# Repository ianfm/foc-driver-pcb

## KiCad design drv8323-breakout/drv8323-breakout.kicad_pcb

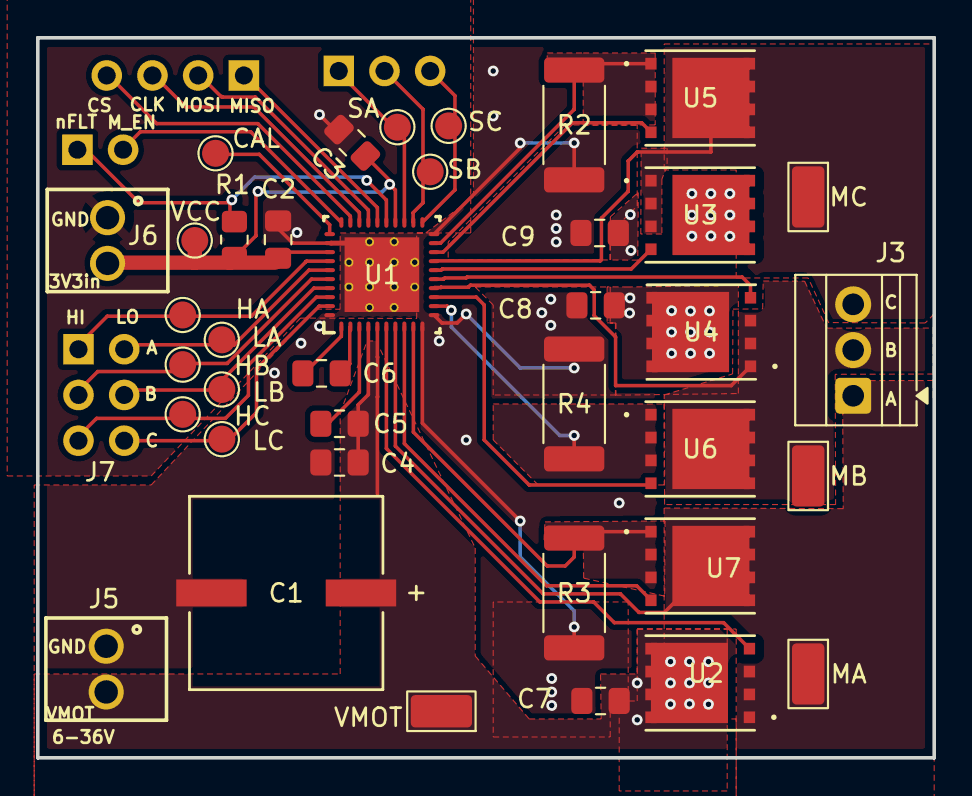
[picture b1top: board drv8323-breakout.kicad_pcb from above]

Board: 2 copper layers, 49.8 x 40.0 mm, 43 parts (0 on the bottom side), 35 nets.

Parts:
C1: 47uF; PCAP_10x10-ELECT_NCA
C2, C5: 1 uF; C_0805_2012Metric_Pad1.18x1.45mm_HandSolder
C3, C4: 0.1 uF; C_0805_2012Metric_Pad1.18x1.45mm_HandSolder
C6: 47 nF; C_0805_2012Metric_Pad1.18x1.45mm_HandSolder
C7, C8, C9: C; C_0805_2012Metric_Pad1.18x1.45mm_HandSolder
CAL: TestPoint; TestPoint_Pad_D1.5mm
HA: TestPoint; TestPoint_Pad_D1.5mm
HB: TestPoint; TestPoint_Pad_D1.5mm
HC: TestPoint; TestPoint_Pad_D1.5mm
J1: Conn_01x02_Pin; PinHeader_1x02_P2.54mm_Vertical
J2: Conn_01x04_Pin; PinHeader_1x04_P2.54mm_Vertical
J3: Screw_Terminal_01x03; TerminalBlock_Xinya_XY308-2.54-3P_1x03_P2.54mm_Horizontal
J4: Conn_01x03_Pin; PinHeader_1x03_P2.54mm_Vertical
J5, J6: Screw_Terminal_01x02; ScrewTerminal
J7: Conn_02x03_Odd_Even; PinHeader_2x03_P2.54mm_Vertical
LA: TestPoint; TestPoint_Pad_D1.5mm
LB: TestPoint; TestPoint_Pad_D1.5mm
LC: TestPoint; TestPoint_Pad_D1.5mm
MA: TestPoint; TestPoint_Keystone_5015_Micro_Mini
MB: TestPoint; TestPoint_Keystone_5015_Micro_Mini
MC: TestPoint; TestPoint_Keystone_5015_Micro_Mini
NT2: NetTie_2; NetTie-2_SMD_Pad0.28mm
R1: R_US; R_0805_2012Metric_Pad1.20x1.40mm_HandSolder
R2, R3, R4: CSS2H-2512K-2L00F; R_2512_6332Metric_Pad1.40x3.35mm_HandSolder
SA: TestPoint; TestPoint_Pad_D1.5mm
SB: TestPoint; TestPoint_Pad_D1.5mm
SC: TestPoint; TestPoint_Pad_D1.5mm
U1: DRV8323HRTAR; RTA0040B
U2, U3, U4, U5, U6, U7: CSD18534Q5A; DQJ8
VCC: TestPoint; TestPoint_Pad_D1.5mm
VMOT: TestPoint; TestPoint_Keystone_5015_Micro_Mini

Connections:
/Motor Control/SPA: R3.1, U1.9 (SPA), U7.1 (S), U7.2 (S), U7.3 (S)
/Motor Control/SPB: R4.1, U1.12 (SPB), U6.1 (S), U6.2 (S), U6.3 (S)
/Motor Control/SPC: R2.1, U1.19 (SPC), U5.1 (S), U5.2 (S), U5.3 (S)
AGND: C2.1, C3.1, J6.1, NT2.2, U1.32 (AGND)
CAL: CAL.1, U1.31 (CAL)
MOT_A: J3.1, MA.1, U1.7 (SHA), U2.1 (S), U2.2 (S), U2.3 (S), U7.5 (D), U7.6 (D), U7.7 (D), U7.8 (D), U7.9 (ep)
MOT_B: J3.2, MB.1, U1.14 (SHB), U4.1 (S), U4.2 (S), U4.3 (S), U6.5 (D), U6.6 (D), U6.7 (D), U6.8 (D), U6.9 (ep)
MOT_C: J3.3, MC.1, U1.17 (SHC), U3.1 (S), U3.2 (S), U3.3 (S), U5.5 (D), U5.6 (D), U5.7 (D), U5.8 (D), U5.9 (ep)
MOT_EN: J1.2, U1.30 (ENABLE)
NFLT: J1.1, R1.2, U1.25 (FAULT_N)
unnamed: C6.1, U1.2 (CPH)
unnamed: C6.2, U1.1 (CPL)
unnamed: U1.6 (GHA), U2.4 (G)
unnamed: U1.15 (GHB), U4.4 (G)
unnamed: U1.16 (GHC), U3.4 (G)
unnamed: U1.8 (GLA), U7.4 (G)
unnamed: U1.13 (GLB), U6.4 (G)
unnamed: U1.18 (GLC), U5.4 (G)
unnamed: C5.2, U1.3 (VCP)
PGND: C1.2, C4.2, C7.1, C8.2, C9.2, J5.1, NT2.1, R2.2, R3.2, R4.2, U1.10 (SNA), U1.11 (SNB), U1.20 (SNC), U1.40 (PGND), U1.41 (PAD)
PWM_HA: HA.1, J7.1, U1.34 (INHA)
PWM_HB: HB.1, J7.3, U1.36 (INHB)
PWM_HC: HC.1, J7.5, U1.38 (INHC)
PWM_LA: J7.2, LA.1, U1.35 (INLA)
PWM_LB: J7.4, LB.1, U1.37 (INLB)
PWM_LC: J7.6, LC.1, U1.39 (INLC)
SNSA: J4.1, SA.1, U1.23 (SOA)
SNSB: J4.2, SB.1, U1.22 (SOB)
SNSC: J4.3, SC.1, U1.21 (SOC)
SPI_CLK: J2.3, U1.28 (VDS_SCLK)
SPI_CS: J2.4, U1.29 (GAIN_SCS_N)
SPI_MISO: J2.1, U1.26 (MODE_SDO)
SPI_MOSI: J2.2, U1.27 (IDRIVE_SDI)
VCC: C2.2, C3.2, J6.2, R1.1, U1.24 (VREF), U1.33 (DVDD), VCC.1
V_MOT: C1.1, C4.1, C5.1, C7.2, C8.1, C9.1, J5.2, U1.4 (VM), U1.5 (VDRAIN), U2.5 (D), U2.6 (D), U2.7 (D), U2.8 (D), U2.9 (ep), U3.5 (D), U3.6 (D), U3.7 (D), U3.8 (D), U3.9 (ep), U4.5 (D), U4.6 (D), U4.7 (D), U4.8 (D), U4.9 (ep), VMOT.1

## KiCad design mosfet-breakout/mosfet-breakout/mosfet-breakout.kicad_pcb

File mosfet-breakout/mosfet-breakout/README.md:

# foc-driver-pcb
BLDC driver aimed at FOC motor control

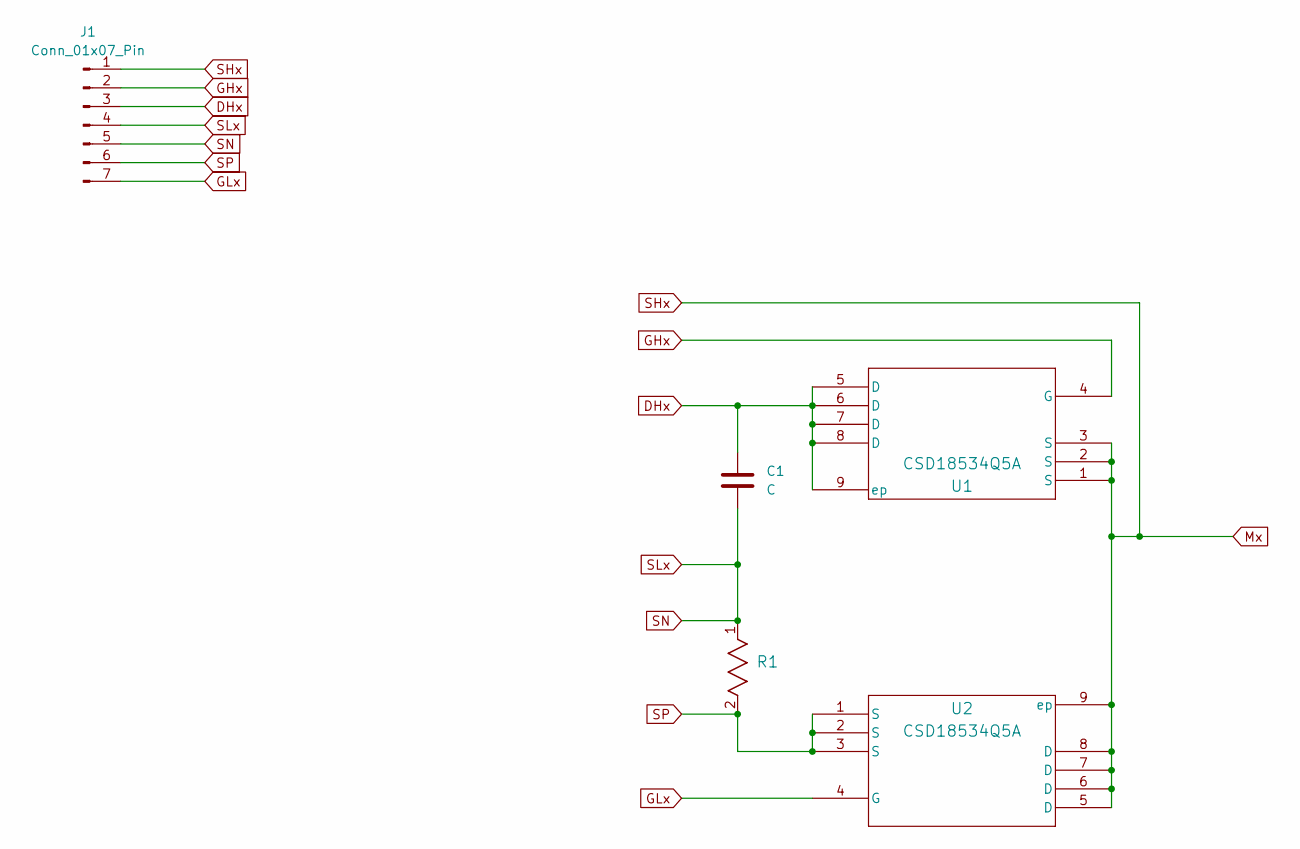
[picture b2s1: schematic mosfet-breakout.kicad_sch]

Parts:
C1: C; C_0805_2012Metric_Pad1.18x1.45mm_HandSolder
J1: Conn_01x07_Pin; PinHeader_1x07_P2.54mm_Vertical
R1: CSS2H-2512K-2L00F; R_2512_6332Metric_Pad1.40x3.35mm_HandSolder
U1, U2: CSD18534Q5A; DQJ8

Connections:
DHx: C1.1, J1.3, U1.5 (D), U1.6 (D), U1.7 (D), U1.8 (D), U1.9 (ep)
GHx: J1.2, U1.4 (G)
GLx: J1.7, U2.4 (G)
Mx: J1.1, U1.1 (S), U1.2 (S), U1.3 (S), U2.5 (D), U2.6 (D), U2.7 (D), U2.8 (D), U2.9 (ep)
SLx: C1.2, J1.4, J1.5, R1.1
SP: J1.6, R1.2, U2.1 (S), U2.2 (S), U2.3 (S)

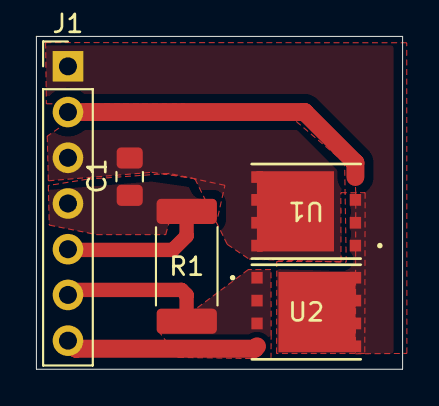
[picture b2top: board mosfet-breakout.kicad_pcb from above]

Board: 2 copper layers, 20.3 x 18.5 mm, 5 parts (0 on the bottom side), 6 nets.

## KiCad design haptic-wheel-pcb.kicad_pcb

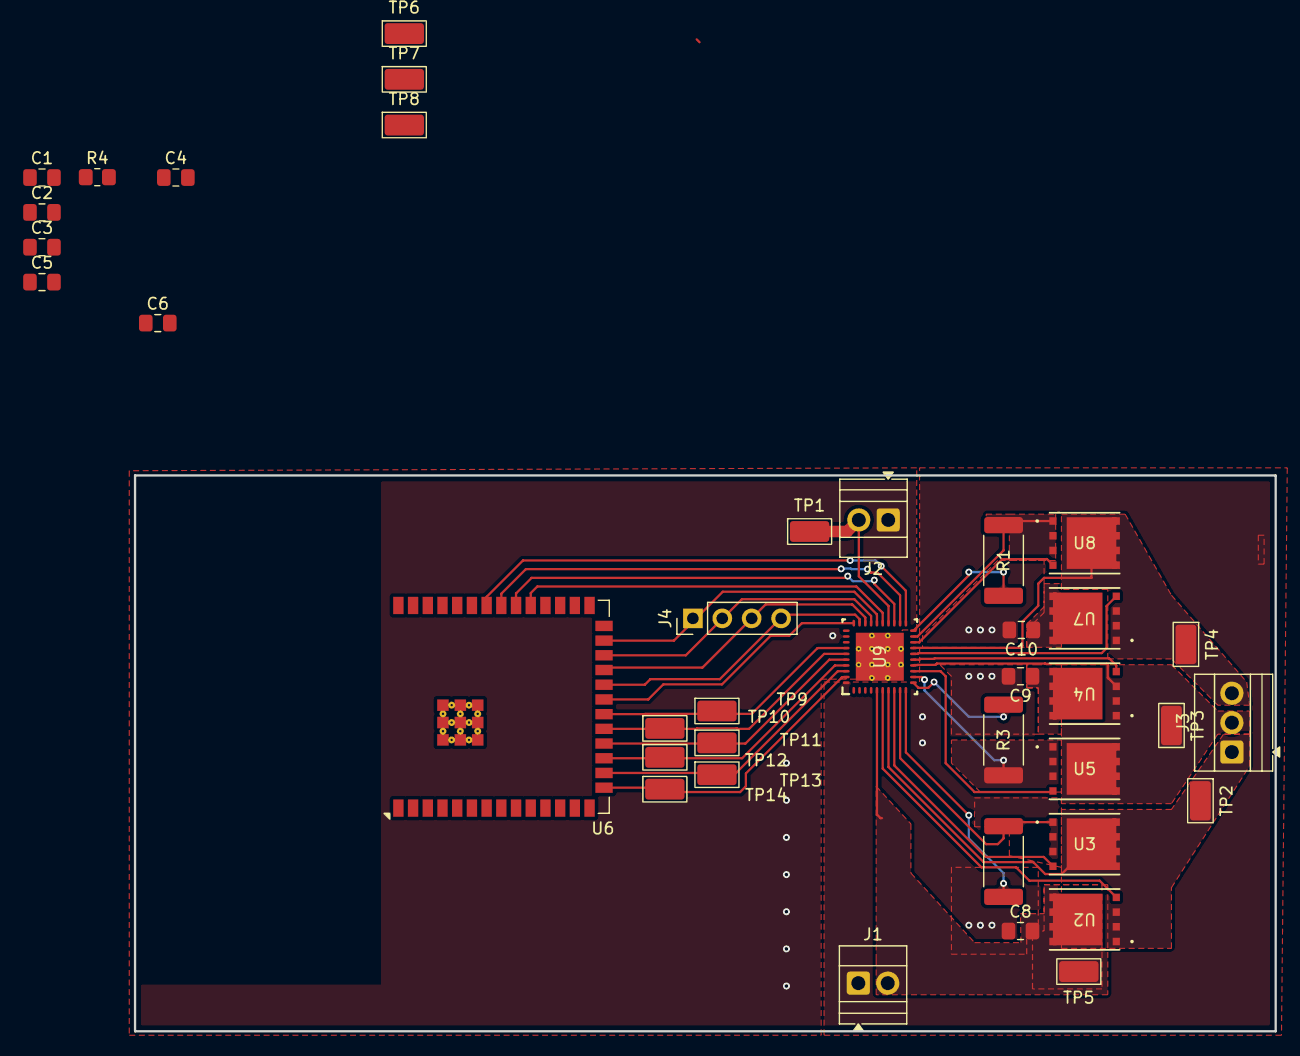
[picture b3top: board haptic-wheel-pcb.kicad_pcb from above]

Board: 2 copper layers, 98.5 x 48.0 mm, 39 parts (0 on the bottom side), 40 nets.

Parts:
C1: 47 nF; C_0805_2012Metric_Pad1.18x1.45mm_HandSolder
C2, C5: 1 uF; C_0805_2012Metric_Pad1.18x1.45mm_HandSolder
C3, C6: 0.1 uF; C_0805_2012Metric_Pad1.18x1.45mm_HandSolder
C4, C8, C9, C10: C; C_0805_2012Metric_Pad1.18x1.45mm_HandSolder
J1, J2: Screw_Terminal_01x02; TerminalBlock_Xinya_XY308-2.54-2P_1x02_P2.54mm_Horizontal
J3: Screw_Terminal_01x03; TerminalBlock_Xinya_XY308-2.54-3P_1x03_P2.54mm_Horizontal
J4: Conn_01x04_Pin; PinHeader_1x04_P2.54mm_Vertical
R1, R2, R3: CSS2H-2512K-2L00F; R_2512_6332Metric_Pad1.40x3.35mm_HandSolder
R4: R_US; R_0805_2012Metric_Pad1.20x1.40mm_HandSolder
TP1, TP2, TP3, TP4, TP5, TP6, TP7, TP8, TP9, TP10, TP11, TP12, TP13, TP14: TestPoint; TestPoint_Keystone_5015_Micro_Mini
U2, U3, U4, U5, U7, U8: CSD18534Q5A; DQJ8
U6: ESP32-S3-WROOM-2
U9: DRV8323HRTAR; RTA0040B

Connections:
/Motor Control/SNA: R2.2, U9.10 (SNA)
/Motor Control/SNB: R3.2, U9.11 (SNB)
/Motor Control/SNC: R1.2, U9.20 (SNC)
/Motor Control/SPA: R2.1, U3.1 (S), U3.2 (S), U3.3 (S), U9.9 (SPA)
/Motor Control/SPB: R3.1, U5.1 (S), U5.2 (S), U5.3 (S), U9.12 (SPB)
/Motor Control/SPC: R1.1, U8.1 (S), U8.2 (S), U8.3 (S), U9.19 (SPC)
AGND: C2.1, C3.1, J2.1, U9.32 (AGND)
MOT_A: J3.1, TP2.1, U2.1 (S), U2.2 (S), U2.3 (S), U3.5 (D), U3.6 (D), U3.7 (D), U3.8 (D), U3.9 (ep), U9.7 (SHA)
MOT_B: J3.2, TP3.1, U4.1 (S), U4.2 (S), U4.3 (S), U5.5 (D), U5.6 (D), U5.7 (D), U5.8 (D), U5.9 (ep), U9.14 (SHB)
MOT_C: J3.3, TP4.1, U7.1 (S), U7.2 (S), U7.3 (S), U8.5 (D), U8.6 (D), U8.7 (D), U8.8 (D), U8.9 (ep), U9.17 (SHC)
MOT_EN: U6.21 (IO13), U9.30 (ENABLE)
NFLT: R4.2, U6.31 (IO38), U9.25 (FAULT_N)
unnamed: U2.4 (G), U9.6 (GHA)
unnamed: U3.4 (G), U9.8 (GLA)
unnamed: U4.4 (G), U9.15 (GHB)
unnamed: U5.4 (G), U9.13 (GLB)
unnamed: U6.1 (GND), U6.40 (GND), U6.41 (GND)
unnamed: U7.4 (G), U9.16 (GHC)
unnamed: U8.4 (G), U9.18 (GLC)
unnamed: C1.1, U9.2 (CPH)
unnamed: C1.2, U9.1 (CPL)
unnamed: C2.2, U9.33 (DVDD)
unnamed: C5.2, U9.3 (VCP)
unnamed: C5.1, C6.1, U9.4 (VM)
PGND: C6.2, C8.1, C9.2, C10.2, J1.1, U9.40 (PGND)
PWM_HA: TP9.1, U6.20 (IO12), U9.34 (INHA)
PWM_HB: TP11.1, U6.18 (IO10), U9.36 (INHB)
PWM_HC: TP13.1, U6.16 (IO46), U9.38 (INHC)
PWM_LA: TP10.1, U6.19 (IO11), U9.35 (INLA)
PWM_LB: TP12.1, U6.17 (IO9), U9.37 (INLB)
PWM_LC: TP14.1, U6.15 (IO3), U9.39 (INLC)
SNSA: TP8.1, U6.32 (MTCK/IO39), U9.23 (SOA)
SNSB: TP7.1, U6.33 (MTDO/IO40), U9.22 (SOB)
SNSC: TP6.1, U6.34 (MTDI/IO41), U9.21 (SOC)
SPI_CLK: J4.3, U6.23 (IO21), U9.28 (VDS_SCLK)
SPI_CS: J4.4, U6.22 (IO14), U9.29 (GAIN_SCS_N)
SPI_MISO: J4.1, U6.25 (IO48), U9.26 (MODE_SDO)
SPI_MOSI: J4.2, U6.24 (IO47), U9.27 (IDRIVE_SDI)
VCC: C3.2, J2.2, R4.1, TP1.1, U9.24 (VREF)
V_MOT: C8.2, C9.1, C10.1, J1.2, TP5.1, U2.5 (D), U2.6 (D), U2.7 (D), U2.8 (D), U2.9 (ep), U4.5 (D), U4.6 (D), U4.7 (D), U4.8 (D), U4.9 (ep), U7.5 (D), U7.6 (D), U7.7 (D), U7.8 (D), U7.9 (ep), U9.5 (VDRAIN)

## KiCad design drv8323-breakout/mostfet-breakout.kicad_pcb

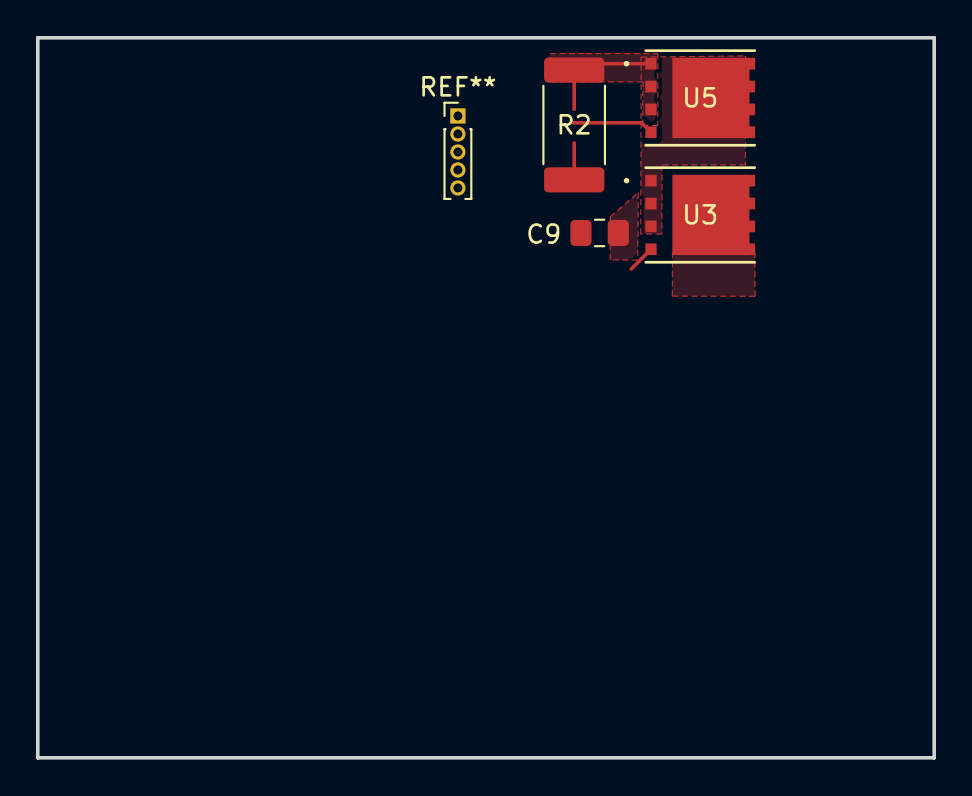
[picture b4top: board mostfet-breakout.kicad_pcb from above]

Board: 2 copper layers, 49.8 x 40.0 mm, 4 parts (0 on the bottom side), 3 nets.

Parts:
C9: C; C_0805_2012Metric_Pad1.18x1.45mm_HandSolder
R2: CSS2H-2512K-2L00F; R_2512_6332Metric_Pad1.40x3.35mm_HandSolder
U3, U5: CSD18534Q5A; DQJ8

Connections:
/Motor Control/SPC: R2.1, U5.1 (S), U5.2 (S), U5.3 (S)
MOT_C: U3.1 (S), U3.2 (S), U3.3 (S), U5.5 (D), U5.6 (D), U5.7 (D), U5.8 (D), U5.9 (ep)
V_MOT: C9.1, U3.5 (D), U3.6 (D), U3.7 (D), U3.8 (D), U3.9 (ep)

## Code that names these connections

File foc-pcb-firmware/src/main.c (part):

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// 1. PIN DEFINITIONS (ESP32-S3-WROOM-1 N16R8 PINOUT)
// =========================================================================
// SPI Interface (DRV8323S Gate Driver Configuration)
#define PIN_SPI_CS          10  // SPI Chip Select (Active LOW)
#define PIN_SPI_CLK         11  // SPI Serial Clock
#define PIN_SPI_MOSI        12  // Master Out Slave In (SDI on DRV8323)
#define PIN_SPI_MISO        13  // Master In Slave Out (SDO on DRV8323)

// I2C Interface (AS5600 Magnetic Encoder)
#define PIN_I2C_SDA         1   // I2C Data
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// =========================================================================
void drv_spi_init(void) {
    spi_bus_config_t buscfg = {
        .miso_io_num     = PIN_SPI_MISO,
        .mosi_io_num     = PIN_SPI_MOSI,
        .sclk_io_num     = PIN_SPI_CLK,
        .quadwp_io_num   = -1,
        .quadhd_io_num   = -1,
        .max_transfer_sz = 32,
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    spi_device_interface_config_t devcfg = {
        .clock_speed_hz = 1000000,    // 1 MHz
        .mode           = 1,          // Mode 1 (CPOL=0, CPHA=1)
        .spics_io_num   = PIN_SPI_CS,
        .queue_size     = 1,
    };

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
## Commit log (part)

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2025-12-30 add nascent kicad project to repo
2025-12-30 wire sense resistors
2026-02-12 routed motor driver fets and shunts
2026-02-14 route all 3 fets with shunts in a vertical line
2026-02-18 using vias on SNA/SPA instead of GxA b/c switching speed
2026-02-18 full gate reroute with zones and sense lines like the layout guide
2026-02-18 selected mcu pins for sense in, SPI
2026-02-19 big layout - lay pgnd and agnd zones and add SPI header pins
2026-03-17 try to remove submodule
2026-03-17 restore submodule content
2026-03-17 update mosfet symbol ep pin
2026-03-18 remove drv module link
2026-03-18 re-add drv8323 breakout
2026-03-18 updated symbols for sanity and PCB for mfg, no DRC errors, only net type ERC errors
2026-03-24 v7 submitted to JLC and ordered 03-24-26
